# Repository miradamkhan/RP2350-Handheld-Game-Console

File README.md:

# RP2350 Handheld Game Console

ECE 362 final project firmware and hardware files for a handheld game console built on the RP2350 Proton board.  
The current codebase includes a game-selection menu and three playable games: Tetris, 2048, and Space Invaders.

This README explains how to download the project, build it as-is, flash it, and test the hardware.

## Project Contents

- `src/`: Main firmware source (menu, games, drivers)
- `platformio.ini`: PlatformIO environment and build filter
- `Project_PCB/`: KiCad schematic and PCB files
- `Gameboy_Project_PCB.zip`: Packaged PCB design files

## Hardware Diagrams

### Schematic

### PCB Layout

## Requirements

- Windows, macOS, or Linux
- [VS Code](https://code.visualstudio.com/) with [PlatformIO IDE](https://platformio.org/install/ide?install=vscode), or PlatformIO Core CLI
- USB connection to the RP2350 board
- Debug/upload setup expected by this repo:
  - `picoprobe` upload/debug workflow (configured in `platformio.ini`)

## 1) Download the Project

### Option A: Clone with Git

```bash
git clone <repo-url>
cd RP2350-Handheld-Game-Console
```

### Option B: Download ZIP

1. Download the repository ZIP from GitHub.
2. Extract it.
3. Open the extracted folder in VS Code.

## 2) Build the Firmware

From the project root:

```bash
pio run -e proton
```

If the build succeeds, PlatformIO will generate firmware in `.pio/build/proton/`.

## 3) Flash to the Board

This project is configured for `picoprobe` upload:

```bash
pio run -e proton -t upload
```

If upload fails, verify:

- `picoprobe` is connected and detected
- The target board is powered
- Wiring and debug pins match your setup

## 4) Optional Serial Monitor

To open UART output:

```bash
pio device monitor -b 115200
```

## 5) Test the Project on Hardware

After flashing, the expected behavior is:

1. Boot splash appears.
2. Game menu appears with three options:
   - TETRIS
   - 2048
   - SPACE INVADERS
3. Joystick up/down changes the selected game.
4. Joystick button launches the selected game.
5. Exiting a game returns to the menu.
6. Leaderboard/high scores persist through EEPROM across resets.

### Input/Output Wiring Reference

- TFT SPI (ILI9341): `GPIO14` SCK, `GPIO15` MOSI, `GPIO13` CS, `GPIO12` DC, `GPIO11` RST
- EEPROM I2C: `GPIO4` SDA, `GPIO5` SCL
- Joystick ADC: `GPIO45` X, `GPIO44` Y, `GPIO6` button
- Extra buttons: `GPIO21` menu, `GPIO26` back
- Speaker PWM: `GPIO30`

## Notes on Scope

This repository is intentionally staying on the current feature set and game implementations.  
Future updates are expected to be small improvements (stability, polish, and maintainability), not major game rewrites.

## Team

- Enio Hysa
- Mir Adam Khan
- Abdulmalik Busari
- Dixon Wagner

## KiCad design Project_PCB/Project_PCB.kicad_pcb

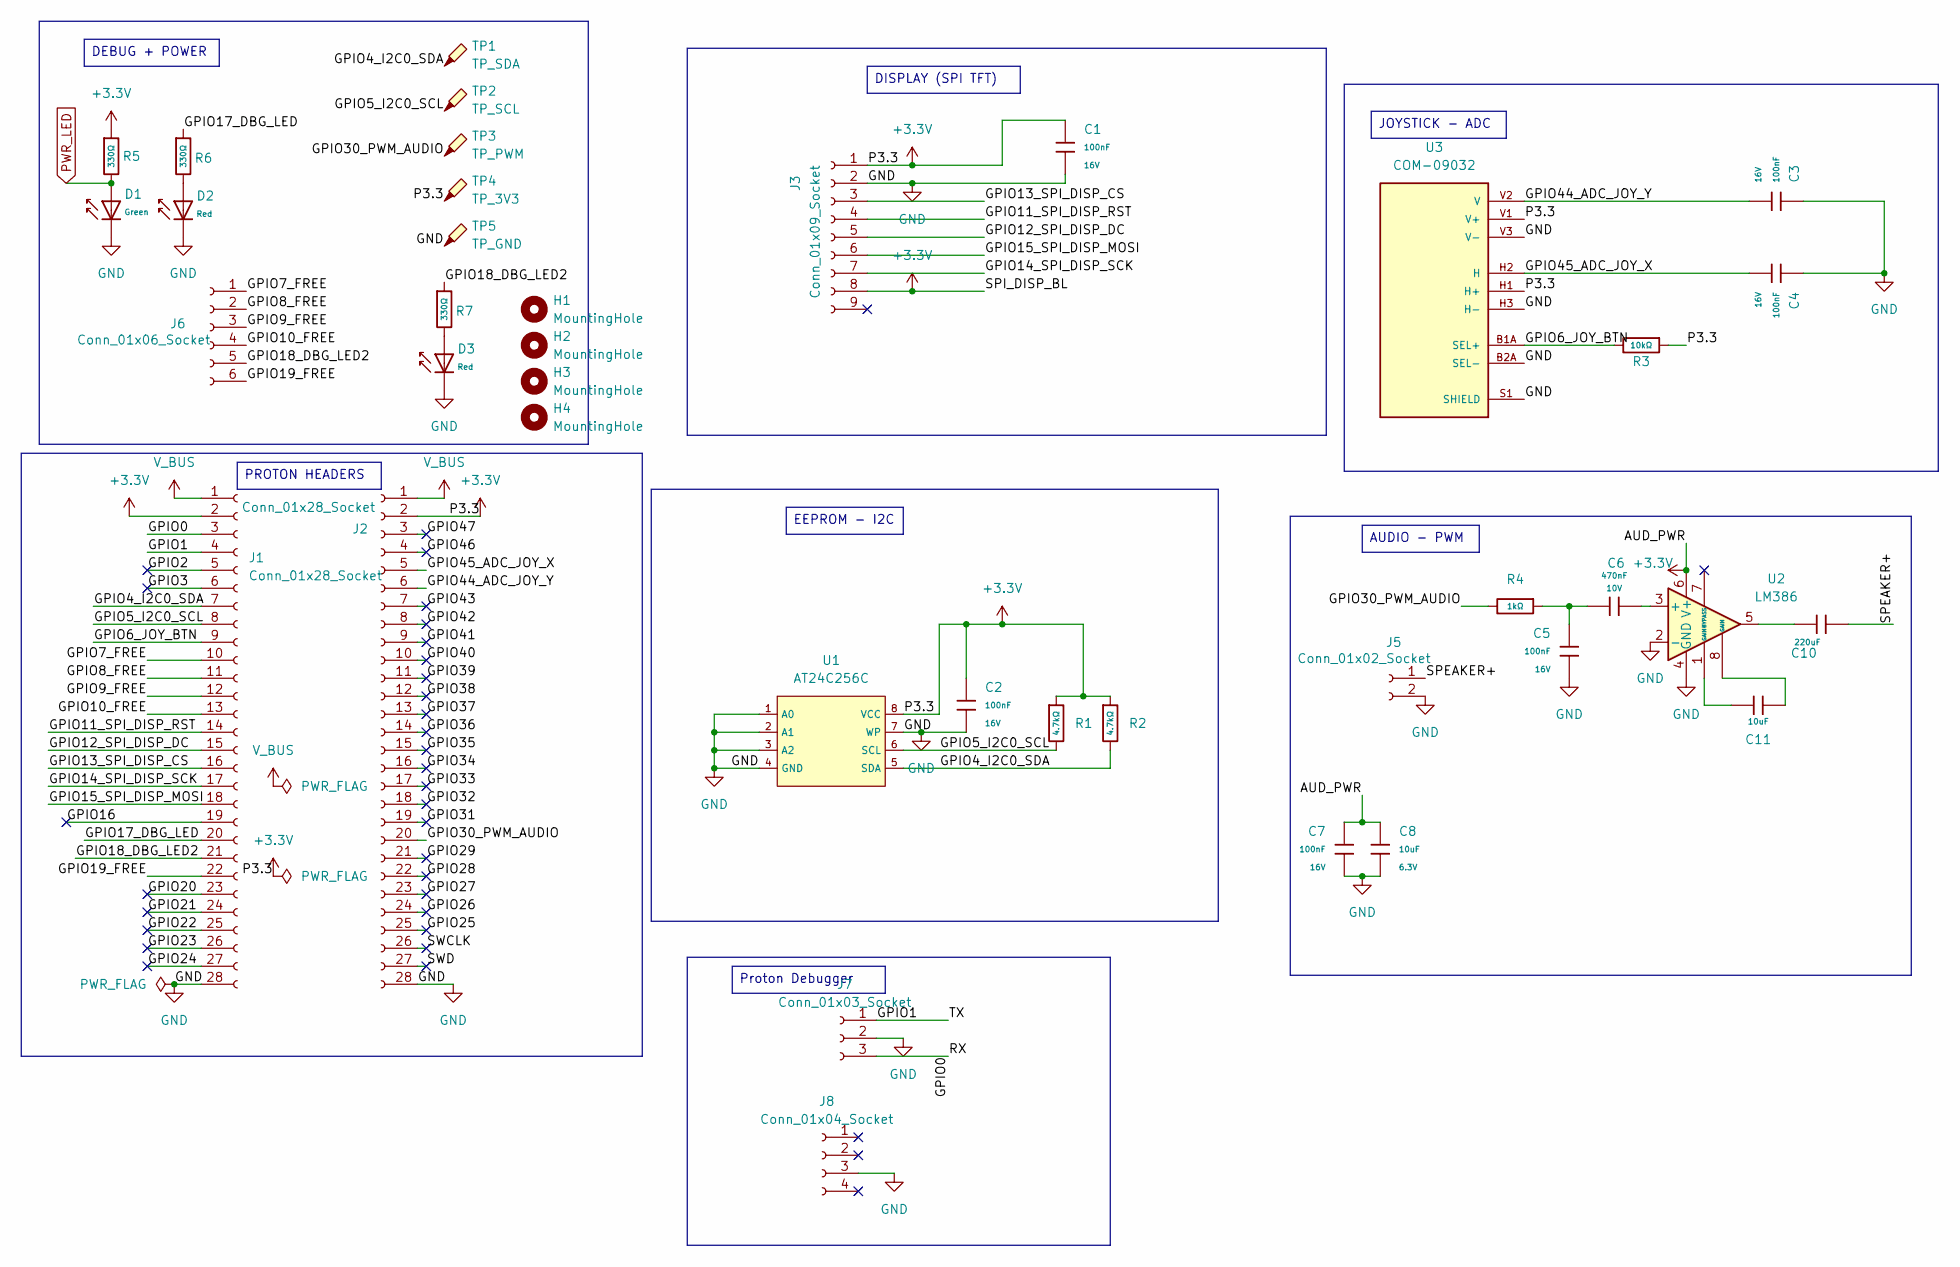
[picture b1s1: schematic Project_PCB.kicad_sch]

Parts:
C1, C2, C3, C4, C5, C7: 100nF; C_0402; Voltage Rated 16V; Tolerance ±10%; Part CL05B104KO5NNNC; LCSC C1525
C6: 470nF; C_0402; Voltage Rated 10V; Tolerance ±10%; Part CL05A474KP5NNNC; LCSC C47339
C8, C11: 10uF; C_0402; Voltage Rated 6.3V; Tolerance ±20%; Part CL05A106MQ5NUNC; LCSC C15525
C10: 220uF; C_0402; Voltage Rated 16V; Tolerance ±10%; Part CL05B104KO5NNNC; LCSC C1525
D1: Green; D_0805; Part KT-0805G; LCSC C2297
D2, D3: Red; D_0805; Forward Voltage (VF) 1.6V~2.6V; Part NCD0805R1; LCSC C84256
H1, H2, H3, H4: MountingHole; MountingHole_3.5mm
J1, J2: Conn_01x28_Socket; PinSocket_1x28_P2.54mm_Vertical
J3: Conn_01x09_Socket; PinSocket_1x09_P2.54mm_Vertical
J5: Conn_01x02_Socket; PinSocket_1x02_P2.54mm_Vertical
J6: Conn_01x06_Socket; PinSocket_1x06_P2.54mm_Vertical
J7: Conn_01x03_Socket; PinSocket_1x03_P2.54mm_Vertical
J8: Conn_01x04_Socket; PinSocket_1x04_P2.54mm_Vertical
R1, R2: 4.7kΩ; R_0402; Overload Voltage (Max) 50V; Tolerance ±1%; Part 0402WGF4701TCE; LCSC C25900
R3: 10kΩ; R_0402; Overload Voltage (Max) 50V; Tolerance ±1%; Part 0402WGF1002TCE; LCSC C25744
R4: 1kΩ; R_0402; Overload Voltage (Max) 50V; Tolerance ±1%; Part 0402WGF1001TCE; LCSC C11702
R5, R6, R7: 330Ω; R_0402; Overload Voltage (Max) 50V; Tolerance ±1%; Part 0402WGF3300TCE; LCSC C25104
TP1: TP_SDA; TestPoint_Pad_D2.0mm
TP2: TP_SCL; TestPoint_Pad_D2.0mm
TP3: TP_PWM; TestPoint_Pad_D2.0mm
TP4: TP_3V3; TestPoint_Pad_D2.0mm
TP5: TP_GND; TestPoint_Pad_D2.0mm
U1: AT24C256C; SOIC-8_L4.9-W3.9-P1.27-LS6.0-BL; Supply Voltage 1.7V~5.5V; Part AT24C256C-SSHL-T; LCSC C6482
U2: LM386; SOIC-8_3.9x4.9mm_P1.27mm
U3: COM-09032; XDCR_COM-09032; PARTREV N/A

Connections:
+3.3V: C1.1, C2.1, C7.1, C8.1, J1.2, J2.2, J3.1, J3.8, R1.1, R2.1, R3.1, R5.1, TP4.1, U1.8 (VCC), U2.6 (V+), U3.H1 (H+), U3.V1 (V+)
/GPIO0: J1.3, J7.3
/GPIO1: J1.4, J7.1
/GPIO2: J1.5
/GPIO3: J1.6
/GPIO4_I2C0_SDA: J1.7, R2.2, TP1.1, U1.5 (SDA)
/GPIO5_I2C0_SCL: J1.8, R1.2, TP2.1, U1.6 (SCL)
/GPIO6_JOY_BTN: J1.9, R3.2, U3.B1A (SEL+)
/GPIO7_FREE: J1.10, J6.1
/GPIO8_FREE: J1.11, J6.2
/GPIO9_FREE: J1.12, J6.3
/GPIO10_FREE: J1.13, J6.4
/GPIO11_SPI_DISP_RST: J1.14, J3.4
/GPIO12_SPI_DISP_DC: J1.15, J3.5
/GPIO13_SPI_DISP_CS: J1.16, J3.3
/GPIO14_SPI_DISP_SCK: J1.17, J3.7
/GPIO15_SPI_DISP_MOSI: J1.18, J3.6
/GPIO16: J1.19
/GPIO17_DBG_LED: J1.20, R6.1
/GPIO18_DBG_LED2: J1.21, J6.5, R7.1
/GPIO19_FREE: J1.22, J6.6
/GPIO20: J1.23
/GPIO21: J1.24
/GPIO22: J1.25
/GPIO23: J1.26
/GPIO24: J1.27
/GPIO25: J2.25
/GPIO26: J2.24
/GPIO27: J2.23
/GPIO28: J2.22
/GPIO29: J2.21
/GPIO30_PWM_AUDIO: J2.20, R4.2, TP3.1
/GPIO31: J2.19
/GPIO32: J2.18
/GPIO33: J2.17
/GPIO34: J2.16
/GPIO35: J2.15
/GPIO36: J2.14
/GPIO37: J2.13
/GPIO38: J2.12
/GPIO39: J2.11
/GPIO40: J2.10
/GPIO41: J2.9
/GPIO42: J2.8
/GPIO43: J2.7
/GPIO44_ADC_JOY_Y: C3.2, J2.6, U3.V2 (V)
/GPIO45_ADC_JOY_X: C4.2, J2.5, U3.H2 (H)
/GPIO46: J2.4
/GPIO47: J2.3
/SPEAKER+: C10.1, J5.1
/SWCLK: J2.26
/SWD: J2.27
GND: C1.2, C2.2, C3.1, C4.1, C5.2, C7.2, C8.2, D1.1, D2.1, D3.1, J1.28, J2.28, J3.2, J5.2, J7.2, J8.3, TP5.1, U1.1 (A0), U1.2 (A1), U1.3 (A2), U1.4 (GND), U1.7 (WP), U2.2 (-), U2.4 (GND), U3.B2A (SEL-), U3.H3 (H-), U3.S1 (SHIELD), U3.S2 (SHIELD), U3.S3 (SHIELD), U3.S4 (SHIELD), U3.V3 (V-)
unnamed: C5.1, C6.2, R4.1
unnamed: C10.2, U2.5
unnamed: C11.1, U2.1 (GAIN)
unnamed: C11.2, U2.8 (GAIN)
unnamed: D2.2, R6.2
unnamed: D3.2, R7.2
unnamed: C6.1, U2.3 (+)
PWR_LED: D1.2, R5.2
V_BUS: J1.1, J2.1

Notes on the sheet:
AUDIO - PWM
EEPROM - I2C
DEBUG + POWER
JOYSTICK - ADC
PROTON HEADERS
DISPLAY (SPI TFT)
Proton Debugger

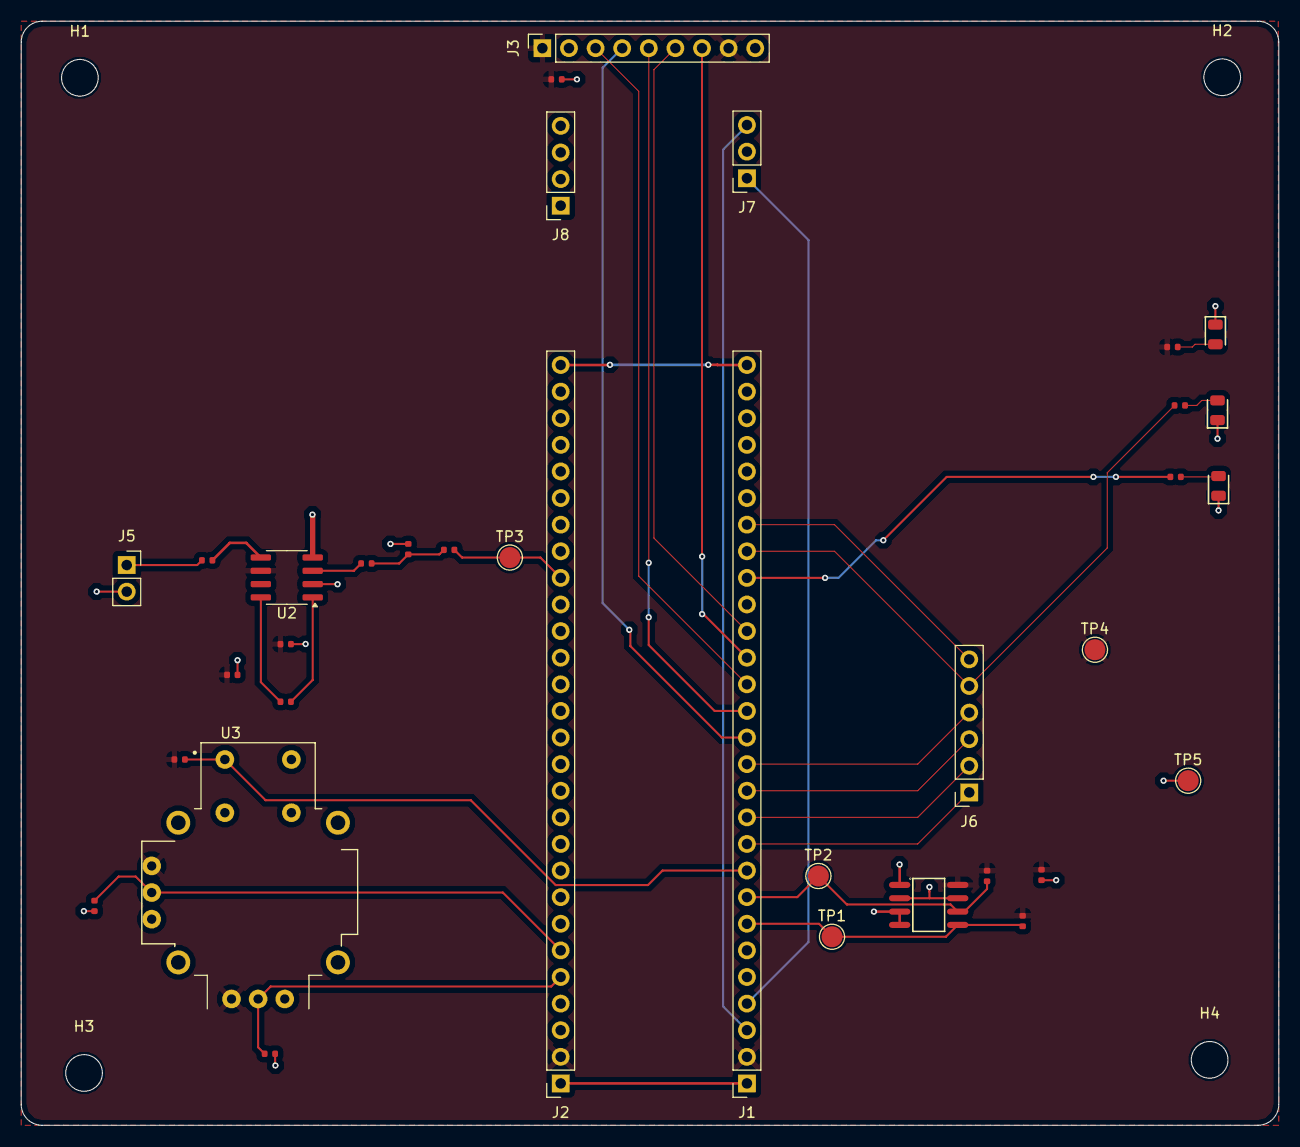
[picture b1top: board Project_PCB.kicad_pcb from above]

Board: 2 copper layers, 120.1 x 105.4 mm, 39 parts (0 on the bottom side), 32 nets.

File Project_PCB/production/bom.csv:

Designator,Footprint,Quantity,Value,LCSC Part #
"C1, C2, C3, C4, C5, C7",C_0402,6,100nF,C1525
C10,C_0402,1,220uF,C1525
"C11, C8",C_0402,2,10uF,C15525
C6,C_0402,1,470nF,C47339
D1,D_0805,1,Green,C2297
"D2, D3",D_0805,2,Red,C84256
"J1, J2",PinSocket_1x28_P2.54mm_Vertical,2,Conn_01x28_Socket,
J3,PinSocket_1x09_P2.54mm_Vertical,1,Conn_01x09_Socket,
J5,PinSocket_1x02_P2.54mm_Vertical,1,Conn_01x02_Socket,
J6,PinSocket_1x06_P2.54mm_Vertical,1,Conn_01x06_Socket,
J7,PinSocket_1x03_P2.54mm_Vertical,1,Conn_01x03_Socket,
J8,PinSocket_1x04_P2.54mm_Vertical,1,Conn_01x04_Socket,
"R1, R2",R_0402,2,4.7kΩ,C25900
R3,R_0402,1,10kΩ,C25744
R4,R_0402,1,1kΩ,C11702
"R5, R6, R7",R_0402,3,330Ω,C25104
TP1,TestPoint_Pad_D2.0mm,1,TP_SDA,
TP2,TestPoint_Pad_D2.0mm,1,TP_SCL,
TP3,TestPoint_Pad_D2.0mm,1,TP_PWM,
TP4,TestPoint_Pad_D2.0mm,1,TP_3V3,
TP5,TestPoint_Pad_D2.0mm,1,TP_GND,
U1,SOIC-8_L4.9-W3.9-P1.27-LS6.0-BL,1,AT24C256C,C6482
U2,SOIC-8_3.9x4.9mm_P1.27mm,1,LM386,
U3,XDCR_COM-09032,1,COM-09032,

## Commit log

2026-03-27 Expand README with project details and features
    Added project overview, features, hardware components, and system architecture details.
2026-03-31 Implement RP2350 Flappy Bird hardware integration.
    Add a complete Pico SDK-style modular codebase with ILI9341 TFT rendering, joystick ADC/button input, PWM audio effects, 24AA32AF EEPROM high-score storage, fixed-timestep game loop, and bring-up tes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
    Made-with: Cursor
2026-03-31 RP2350 Tetris implementation
2026-04-02 Update Flappy and Tetris to final hardware pin map.
    Remap SPI, I2C, ADC, GPIO button, PWM audio, and debug LED pins to the provided RP2350 wiring, and remove unused TFT backlight pin handling.
    Made-with: Cursor
2026-04-02 Added PCB files
2026-04-02 Removed a wrong file
2026-04-02 Revise README for clarity and visual appeal
    Updated README with enhanced formatting, added emojis, and improved project details.
2026-04-06 Platformio Init File
2026-04-06 Main Menu Functionality Added
2026-04-06 test day 1
2026-04-09 working code 1
2026-04-10 improved tetris
2026-04-10 Flappy Bird Waiting Phase
2026-04-10 Fixed Menu Bug
2026-04-10 fixed games and sounds
2026-04-10 updated read me
2026-04-11 Correct spelling of Abdulmalik Busari
2026-04-16 Add files via upload
    Initial design of the Game Boy case
